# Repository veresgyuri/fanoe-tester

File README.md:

# FÁNOE tester

**Status:** Under active development - started by Gyuri on 2026. july-

Sorry folks, this repo comes with Hungarian comments only 🙂<br> 

Ez a repository egy ESP32-S3 alapú, CircuitPython-ban futó diagnosztikai eszközhöz készült firmware-t és kapcsolódó forrásfájlokat tartalmazza.  
### A projekt célja egy billentyűzettel és egy kis TFT kijelzővel működő, menüvezérelt tesztműszer összeállítása.  

<table>
  <tr>
    <td align="center">
      
    </td>
    <td align="center">
      
    </td>
   </tr>
</table>

## Rövid bemutató

A rendszer a következő funkciókat szolgálja:
- ellenállás mérés [0-500Ω]
- relé működtetéshez kimenet vezérlés
- kontaktus bemenet időméréssel
- teljes mérési ciklus futtatása
- menüvezérelt felület a kijelzőn
- billentyűzetes navigáció
- beállítások, információs oldalak és mérési üzemmódok
- CircuitPython-alapú futtatás ESP32-S3 hardveren

A fő program a [code.py](code.py) fájlban található, a menüstruktúra a [menu_data.py](menu_data.py), a kijelző üzenetek a [tft_messages.py](tft_messages.py) fájlban vannak definiálva. A rendszerindítási viselkedést a [boot.py](boot.py) fájl kezeli.

## Kapcsolási rajz
```
                      TÁPFESZÜLTSÉG
PullUp resistors          REPL
   on the PCB              ↓
     ↓                   USB-C                  2.25" SPI TFT
          K           ┌────┬──┬────┐      ┌──────────────────────────┐
    5,6k -E--Column1-─┤IO1 └──┘IO13├──────┤SCL                      +├─ 3V3
    5,6k -Y--Column2-─┤IO2     IO12├──────┤SDA                      -├─ GND  
    5,6k -P--Column3-─┤IO3     IO11├──────┤RST      ST7789SP3        │  
          A ── Row1-──┤IO4     IO10├──────┤DC                        │   
          D ── Row2-──┤IO5     IO9 ├──────┤CS         76*284         │   
                      │        IO8 ├──────┤BL                        │ 
 [ENTER] [LEFT] [UP]  │            │      └──────────────────────────┘
 [ESC] [RIGHT] [DOWN] │  ESP32-S3  │  
                      │ Super Mini │  3V3
                      │            │  ┌┴┐
 NO Contact->-DigIn ──┤IO6         │  │ │150     
                      │            │  └┬┘ 
    Relay-<-DigOut--──┤IO7    *IO14├───┴──-<---[Rx]---GND
                      └────────────┘
```

## Hardver

A projekthez használt hardverösszetevők:
- ESP32-S3 Super Mini alaplap
- 6 gombos Protecta mátrix billentyűzet
- 76×284 pixel-es ST7789 vezérlésű TFT kijelző
- USB-C kapcsolat fejlesztéshez / hibakereséshez

## Fájlok és szerepük

- [code.py](code.py) – a fő alkalmazás, a kijelzővezérlés, billentyűzetkezelés és a menü,- és méréslogika.
- [menu_data.py](menu_data.py) – a menüfa és a felhasználói felület adatai.
- [tft_messages.py](tft_messages.py) - A szines kijelző üzenetei.
- [boot.py](boot.py) – induláskor beállítja a felhasználói / fejlesztői módot, és kezeli az USB-meghajtó viselkedését.
- [instructions/](instructions/) – hardver- és szoftver-specifikus dokumentációk.
- [fonts/](fonts/) – a kijelzőn használt betűtípusok, karakterek.
- [lib/](lib/) – a CircuitPython futtatáshoz szükséges könyvtárak.

### Az összes kód és a kapcsolódó fájlok zöme - ingyenes Ai támogatással készült.
Ezek gerincét a Claude (Sonet5 - medium) free alkotta, webböngészős projekt környezetben futtatva.  
A nyelvi modell működési irányát az [AGENTS.md](AGENTS.md) és a [.copilot-instructions.md](.copilot-instructions.md) jelöli ki.

A REPL megjelenítése, a fájlok gyors feltöltése és ellenőrzőse a Thonny 4.1.7 programmal történt.

A VsCode 1.13x.x főként a szöveges szerkesztésben és a verzió követésben segédkezett.

## Telepítés és futtatás

1. Telepítsd a CircuitPython firmware-t az ESP32-S3 Super Mini boardra.
2. Másold a repository tartalmát a CIRCUITPY meghajtóra.
3. Győződj meg róla, hogy a szükséges könyvtárak a megfelelő helyen vannak a [lib/](lib/) mappában.
4. Indítsd újra a készüléket.
5. A [boot.py](boot.py) alapján a rendszer felhasználói vagy fejlesztői üzemmódban indulhat.

## Üzemmódok

A bootfázisban a GPIO21-es kapcsoló állapota alapján dönt a rendszer:
- felhasználói mód: az USB meghajtó inaktív, a program számára engedélyezett a fájlírás
- fejlesztői mód: az USB meghajtó aktív, ami a fejlesztéshez hasznos

## Fejlesztés, áttekintés

A projekt dokumentációja az [instructions/](instructions/) mappában található.  
A fényképes dokumentálás az [images/](images/) mappában található.   

## Megjegyzés

Ez a projekt jelenleg aktív fejlesztés alatt áll, így a funkciók és a menüelemek folyamatosan változnak.

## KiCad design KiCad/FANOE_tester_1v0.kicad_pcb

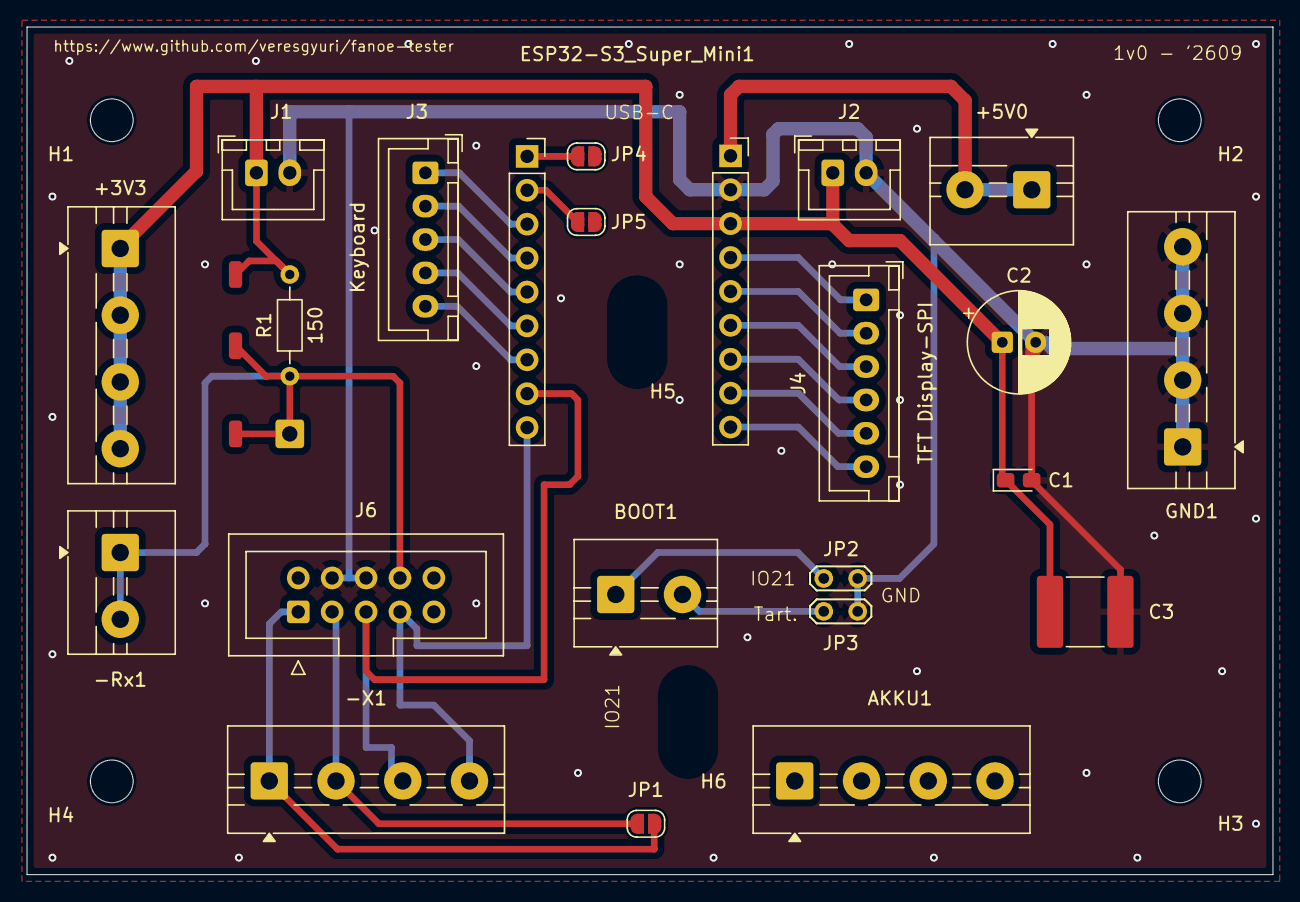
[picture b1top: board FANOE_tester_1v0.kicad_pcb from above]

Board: 2 copper layers, 93.3 x 63.5 mm, 33 parts (0 on the bottom side), 23 nets.

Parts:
+3V3: Screw_Terminal_01x04; TerminalBlock_MaiXu_MX126-5.0-04P_1x04_P5.00mm
+5V0: Screw_Terminal_01x02; TerminalBlock_MaiXu_MX126-5.0-02P_1x02_P5.00mm
-Rx1: Screw_Terminal_01x02; TerminalBlock_MaiXu_MX126-5.0-02P_1x02_P5.00mm
-X1: Screw_Terminal_01x04; TerminalBlock_MaiXu_MX126-5.0-04P_1x04_P5.00mm
AKKU1: Screw_Terminal_01x04; TerminalBlock_MaiXu_MX126-5.0-04P_1x04_P5.00mm
BOOT1: Screw_Terminal_01x02; TerminalBlock_MaiXu_MX126-5.0-02P_1x02_P5.00mm
C1: C_Polarized_Small; CP_EIA-2012-12_Kemet-R_HandSolder
C2: CP_Radial_D7.5mm_P2.50mm
C3: C_Small; C_2220_5750Metric_Pad1.97x5.40mm_HandSolder
ESP32-S3_Super_Mini1, ESP32-S3_Super_Mini2: Conn_01x09; PinSocket_1x09_P2.54mm_Vertical
GND1: Screw_Terminal_01x04; TerminalBlock_MaiXu_MX126-5.0-04P_1x04_P5.00mm
H1, H2, H3, H4, H5, H6: MountingHole_3.2mm_M3
J1, J2: Conn_01x02; JST_XH_B2B-XH-A_1x02_P2.50mm_Vertical
J3: Keyboard; JST_XH_B5B-XH-A_1x05_P2.50mm_Vertical
J4: TFT Display-SPI; JST_XH_B6B-XH-A_1x06_P2.50mm_Vertical
J6: Conn_02x05_Odd_Even; IDC-Header_2x05_P2.54mm_Vertical
JP1, JP4, JP5: SolderJumper_2_Open; SolderJumper-2_P1.3mm_Open_RoundedPad1.0x1.5mm
JP2, JP3: Jumper_2_Open; TestPoint_2Pads_Pitch2.54mm_Drill0.8mm
Ohm1: SolderWire-0.5sqmm_1x01_D0.9mm_OD2.1mm
Ohm2, Ohm3, Ohm4: SolderWirePad_1x01_SMD_1x2mm
R1: 150; R_Axial_DIN0204_L3.6mm_D1.6mm_P7.62mm_Horizontal

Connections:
-3V3: +3V3.1, +3V3.2, +3V3.3, +3V3.4, C1.1, C2.1, C3.1, ESP32-S3_Super_Mini2.3 (+3V3-), J1.1, J2.1, Ohm4.1, R1.2
GND: C1.2, C2.2, C3.2, ESP32-S3_Super_Mini2.2 (GND-), GND1.1, GND1.2, GND1.3, GND1.4, J1.2, J2.2, J6.4, J6.6, JP2.2 (B), JP3.2 (B)
unnamed: +5V0.1, +5V0.2, ESP32-S3_Super_Mini2.1 (+5V-)
unnamed: -Rx1.1, -Rx1.2, J6.8, Ohm1.1, Ohm2.1, Ohm3.1, R1.1
unnamed: -X1.1, J6.1, JP1.2 (B)
unnamed: -X1.2, J6.3, JP1.1 (A)
unnamed: -X1.3, ESP32-S3_Super_Mini1.8 (-IO6), J6.5
unnamed: -X1.4, ESP32-S3_Super_Mini1.9 (-IO7), J6.7
unnamed: BOOT1.1, JP2.1 (A)
unnamed: BOOT1.2, JP3.1 (A)
unnamed: ESP32-S3_Super_Mini1.3 (-IO1), J3.1 (Column1-)
unnamed: ESP32-S3_Super_Mini1.4 (-IO2), J3.2 (Column2-)
unnamed: ESP32-S3_Super_Mini1.5 (-IO3), J3.3 (Column3-)
unnamed: ESP32-S3_Super_Mini1.6 (-IO4), J3.4 (Row1-)
unnamed: ESP32-S3_Super_Mini1.7 (-IO5), J3.5 (Row2-)
unnamed: ESP32-S3_Super_Mini1.2 (-RX), JP5.1 (A)
unnamed: ESP32-S3_Super_Mini1.1 (-TX), JP4.1 (A)
unnamed: ESP32-S3_Super_Mini2.9 (IO8-), J4.6 (-BL)
unnamed: ESP32-S3_Super_Mini2.8 (IO9-), J4.5 (-CS)
unnamed: ESP32-S3_Super_Mini2.7 (IO10-), J4.4 (-DC)
unnamed: ESP32-S3_Super_Mini2.6 (IO11-), J4.3 (-RST)
unnamed: ESP32-S3_Super_Mini2.5 (IO12-), J4.2 (-SDA)
unnamed: ESP32-S3_Super_Mini2.4 (IO13-), J4.1 (-SCL)
